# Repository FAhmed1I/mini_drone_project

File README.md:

<h1>249g Mini Drone Project for taking pictures when Hiking</h1>
Using RunCam Thumb 2 camera

Small form factor for easy transport & setup. HD action camera to get pictures. Custom hardware for the love of the game

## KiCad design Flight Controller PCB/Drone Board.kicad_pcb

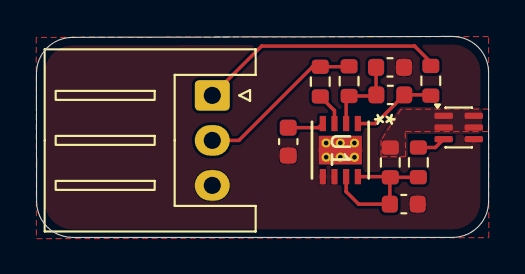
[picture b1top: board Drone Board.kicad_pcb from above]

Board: 2 copper layers, 25.1 x 11.2 mm, 12 parts (0 on the bottom side), 10 nets.

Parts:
C1: 330n; C_0603_1608Metric
C2, C3, C4: 100n; C_0603_1608Metric
J1: Conn_01x03; JST_XH_S3B-XH-A_1x03_P2.50mm_Horizontal
Q1: Si1442DH; SOT-363_SC-70-6
R1, R5: 100; R_0603_1608Metric
R2: 260; R_0603_1608Metric
R3: 160; R_0603_1608Metric
R4: 1k; R_0603_1608Metric
U1: BQ29200DRBR; DRB8_1P6X2P4

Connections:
/BMS/BMS_VDD: C4.1, R4.1, R5.1, U1.7 (VDD), U1.8 (OUT)
/BMS/VBATT: Q1.1 (D), Q1.2 (D), Q1.5 (D), Q1.6 (D), R5.2
unnamed: J1.1, R3.1
unnamed: J1.2, R1.1, R2.1
unnamed: Q1.3 (G), R4.2
unnamed: C1.1, U1.4 (CD)
unnamed: C2.1, C3.2, R2.2, U1.2 (VC1)
unnamed: R1.2, U1.3 (VC1_CB)
unnamed: C3.1, R3.2, U1.1 (VC2)
PGND: C1.2, C2.2, C4.2, J1.3, Q1.4 (S), U1.5 (GND), U1.6 (*CB_EN), U1.9 (EPAD)
